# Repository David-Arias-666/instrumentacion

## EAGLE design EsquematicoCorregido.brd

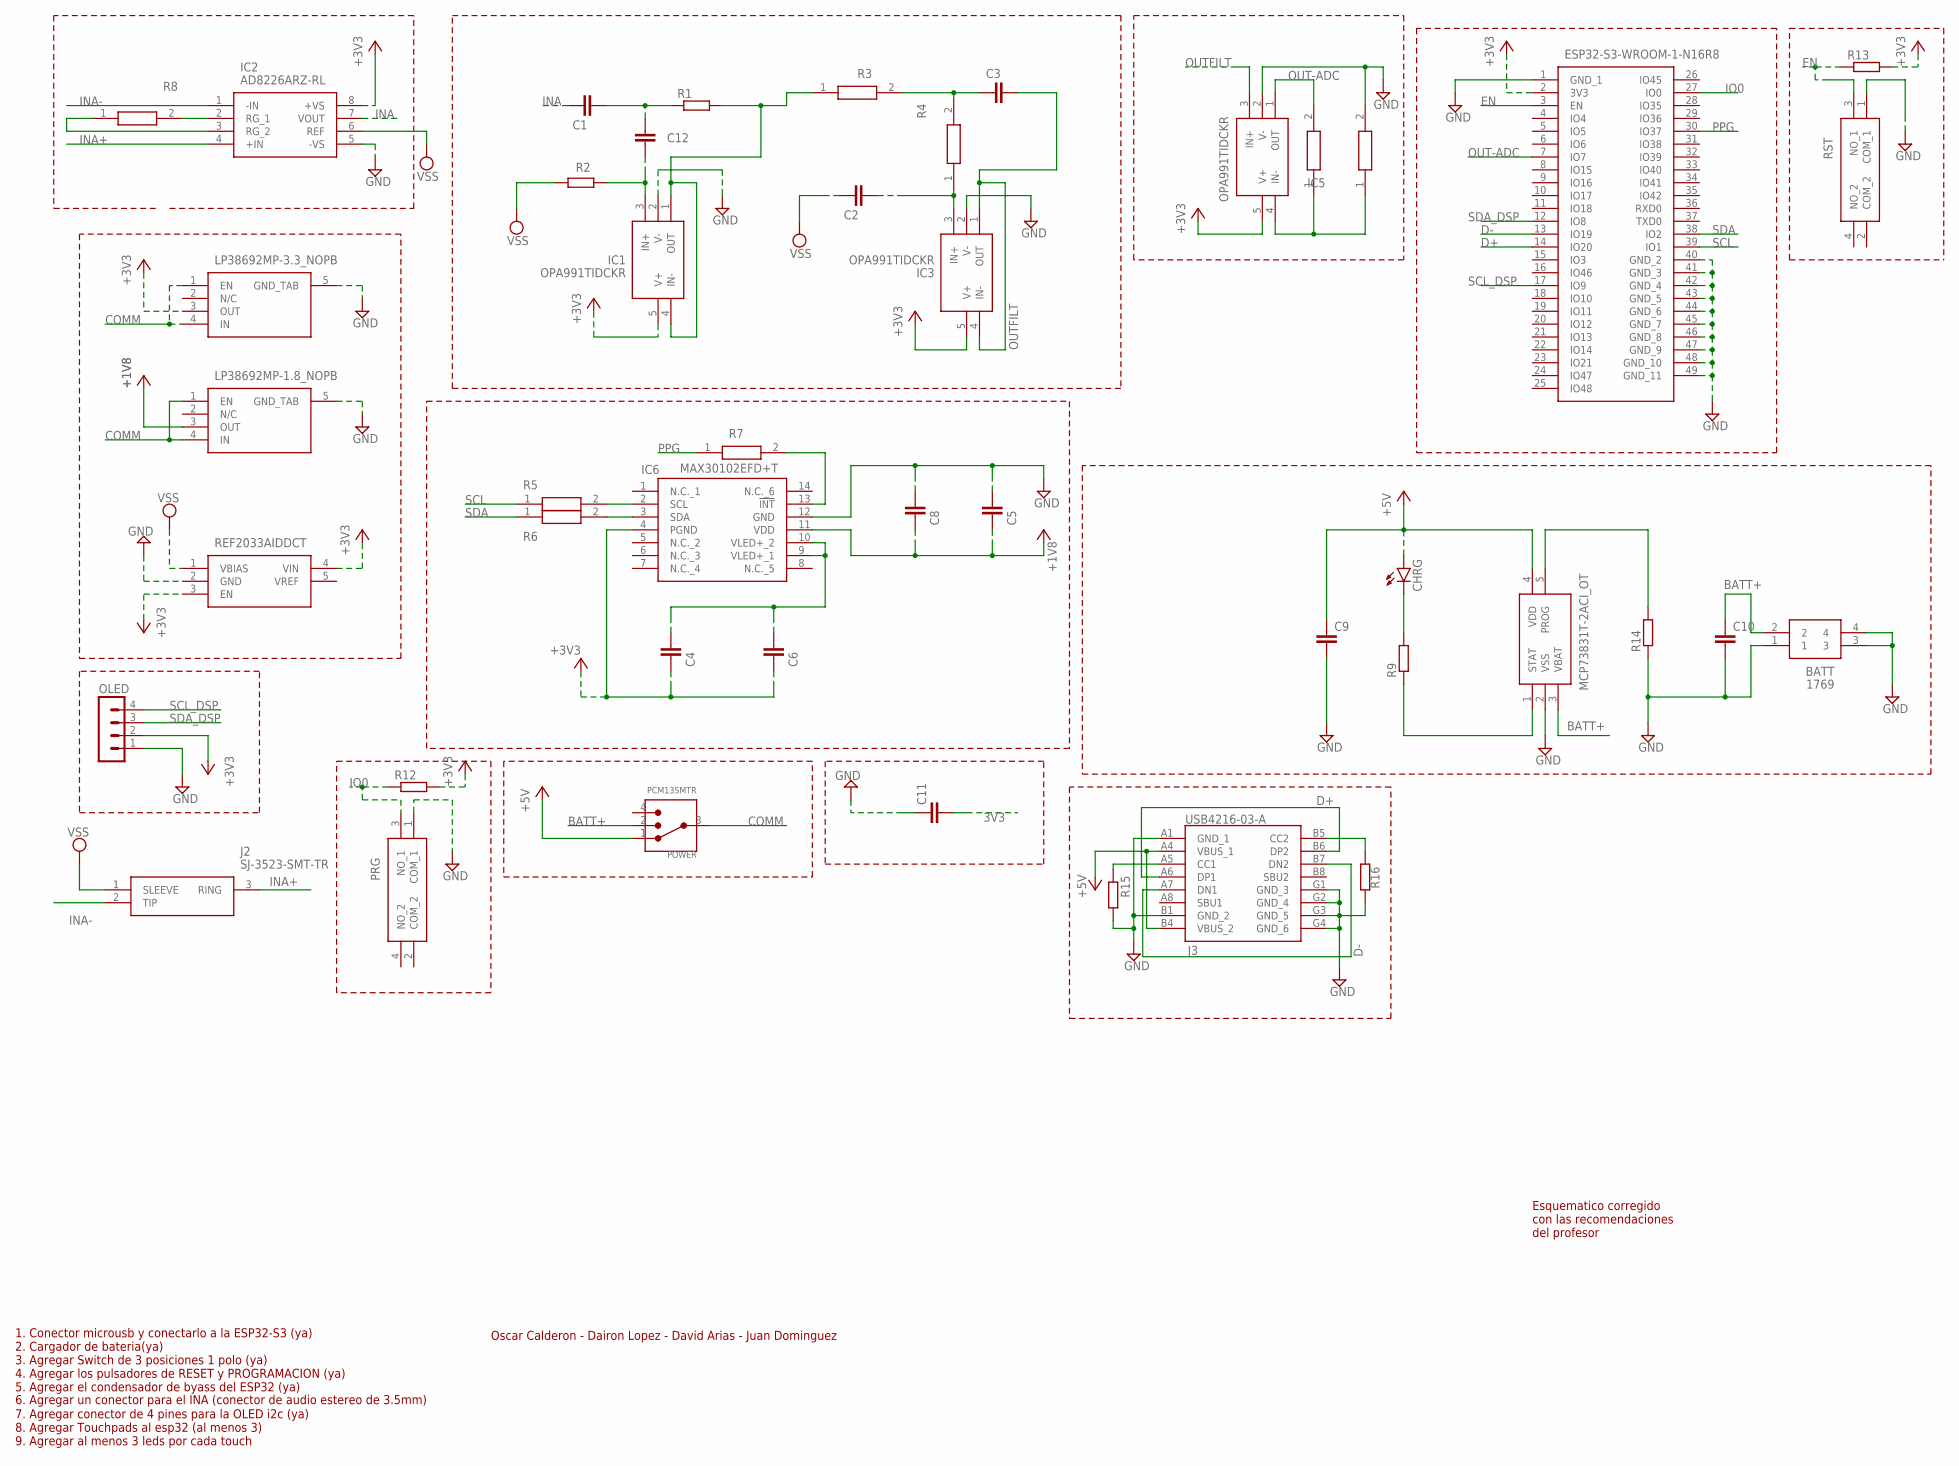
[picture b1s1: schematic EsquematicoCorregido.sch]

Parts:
BATT: 1769
C1, C2, C3, C4, C5, C6, C8, C9, C10, C11, C12: C-EUC0805; C0805
CHRG: LEDCHIP-LED0805; CHIP-LED0805
IC1, IC3, IC5: OPA991TIDCKR; SOT65P210X110-5N
IC2: AD8226ARZ-RL; SOIC127P600X175-8N
IC4: ESP32-S3-WROOM-1-N16R8; ESP32S3WROOM1N16R8
IC6: MAX30102EFD+T; MAX30102EFDT
IC7: LP38692MP-3.3_NOPB; SOT150P700X180-5N
IC8: LP38692MP-1.8_NOPB; SOT150P700X180-5N
IC9: REF2033AIDDCT; SOT95P280X110-5N
IC10: MCP73831T-2ACI_OT; SOT95P270X145-5N
J2: SJ-3523-SMT-TR; SJ3523SMTTR
J3: USB4216-03-A; USB421603A
OLED: MA04-1
POWER: PCM13SMTR; SW_PCM13SMTR
PRG: PTS526SK15SMTR2_LFS; PTS526SK15SMTR2LFS
R1, R2, R9, R12, R13, R14, R15, R16: R-EU_R0805; R0805
R3, R4: ERA-6ARW122V; ERA6AEB101V
R5, R6, R7: CRCW08051K00FKTAHP; RESC2012X60N
R8: RN73H1JTTD1043B50; RESC1608X55N
R10, R11: CRCW0805220RFKTAHP; RESC2012X60N
RST: PTS526SK15SMTR2_LFS; PTS526SK15SMTR2LFS

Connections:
+1V8: C5.1, C8.1, IC6.11 (VDD), IC8.3 (OUT)
+5V: C9.1, CHRG.A, IC10.4 (VDD), J3.A4 (VBUS_1), J3.B4 (VBUS_2), POWER.1
BATT+: BATT.2, C10.1, IC10.3 (VBAT), POWER.2
COMM: IC7.1 (EN), IC7.4 (IN), IC8.1 (EN), IC8.4 (IN), POWER.3
D+: IC4.14 (IO20), J3.A6 (DP1), J3.B6 (DP2)
D-: IC4.13 (IO19), J3.A7 (DN1), J3.B7 (DN2)
EN: IC4.3 (EN), R13.1, RST.3 (NO_1)
GND: BATT.1, BATT.3, BATT.4, C5.2, C8.2, C9.2, C10.2, C11.1, IC1.2 (V-), IC2.5 (-VS), IC3.2 (V-), IC4.1 (GND_1), IC4.40 (GND_2), IC4.41 (GND_3), IC4.42 (GND_4), IC4.43 (GND_5), IC4.44 (GND_6), IC4.45 (GND_7), IC4.46 (GND_8), IC4.47 (GND_9), IC4.48 (GND_10), IC4.49 (GND_11), IC5.2 (V-), IC6.12 (GND), IC7.5 (GND_TAB), IC8.5 (GND_TAB), IC9.2 (GND), IC10.2 (VSS), J3.A1 (GND_1), J3.B1 (GND_2), J3.G1 (GND_3), J3.G2 (GND_4), J3.G3 (GND_5), J3.G4 (GND_6), OLED.1, PRG.1 (COM_1), R11.2, R14.1, R15.2, R16.1, RST.1 (COM_1)
INA: C1.1, IC2.7 (VOUT)
INA+: IC2.4 (+IN), J2.3 (RING)
INA-: IC2.1 (-IN), J2.2 (TIP)
IO0: IC4.27 (IO0), PRG.3 (NO_1), R12.1
unnamed: C3.2, R3.2, R4.2
unnamed: C1.2, C12.2, R1.1
unnamed: C12.1, IC1.3 (IN+), R2.2
unnamed: C2.2, IC3.3 (IN+), R4.1
unnamed: IC5.4 (IN-), R10.1, R11.1
unnamed: IC1.1 (OUT), IC1.4 (IN-), R1.2, R3.1
unnamed: IC2.2 (RG_1), R8.2
unnamed: IC6.13 (!INT), R7.2
unnamed: C4.2, C6.2, IC6.9 (VLED+_1), IC6.10 (VLED+_2)
unnamed: IC2.3 (RG_2), R8.1
unnamed: IC6.3 (SDA), R6.2
unnamed: IC6.2 (SCL), R5.2
unnamed: CHRG.C, R9.2
unnamed: J3.A5 (CC1), R15.1
unnamed: IC10.5 (PROG), R14.2
unnamed: IC10.1 (STAT), R9.1
unnamed: J3.B5 (CC2), R16.2
OUT-ADC: IC4.7 (IO7), IC5.1 (OUT), R10.2
OUTFILT: C3.1, IC3.1 (OUT), IC3.4 (IN-), IC5.3 (IN+)
PPG: IC4.30 (IO37), R7.1
SCL: IC4.39 (IO1), R5.1
SCL_DSP: IC4.17 (IO9), OLED.4
SDA: IC4.38 (IO2), R6.1
SDA_DSP: IC4.12 (IO8), OLED.3
VSS: C2.1, IC2.6 (REF), IC9.1 (VBIAS), J2.1 (SLEEVE), R2.1

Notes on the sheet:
Esquematico corregido con las recomendaciones del profesor
Oscar Calderon - Dairon Lopez - David Arias - Juan Dominguez
1. Conector microusb y conectarlo a la ESP32-S3 (ya) 2. Cargador de bateria(ya) 3. Agregar Switch de 3 posiciones 1 polo (ya) 4. Agregar los pulsadores de RESET y PROGRAMACION (ya) 5. Agregar el condensador de byass del ESP32 (ya)
6. Agregar un conector para el INA (conector de audio estereo de 3.5mm)
7. Agregar conector de 4 pines para la OLED i2c (ya) 8. Agregar Touchpads al esp32 (al menos 3) 9. Agregar al menos 3 leds por cada touch

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
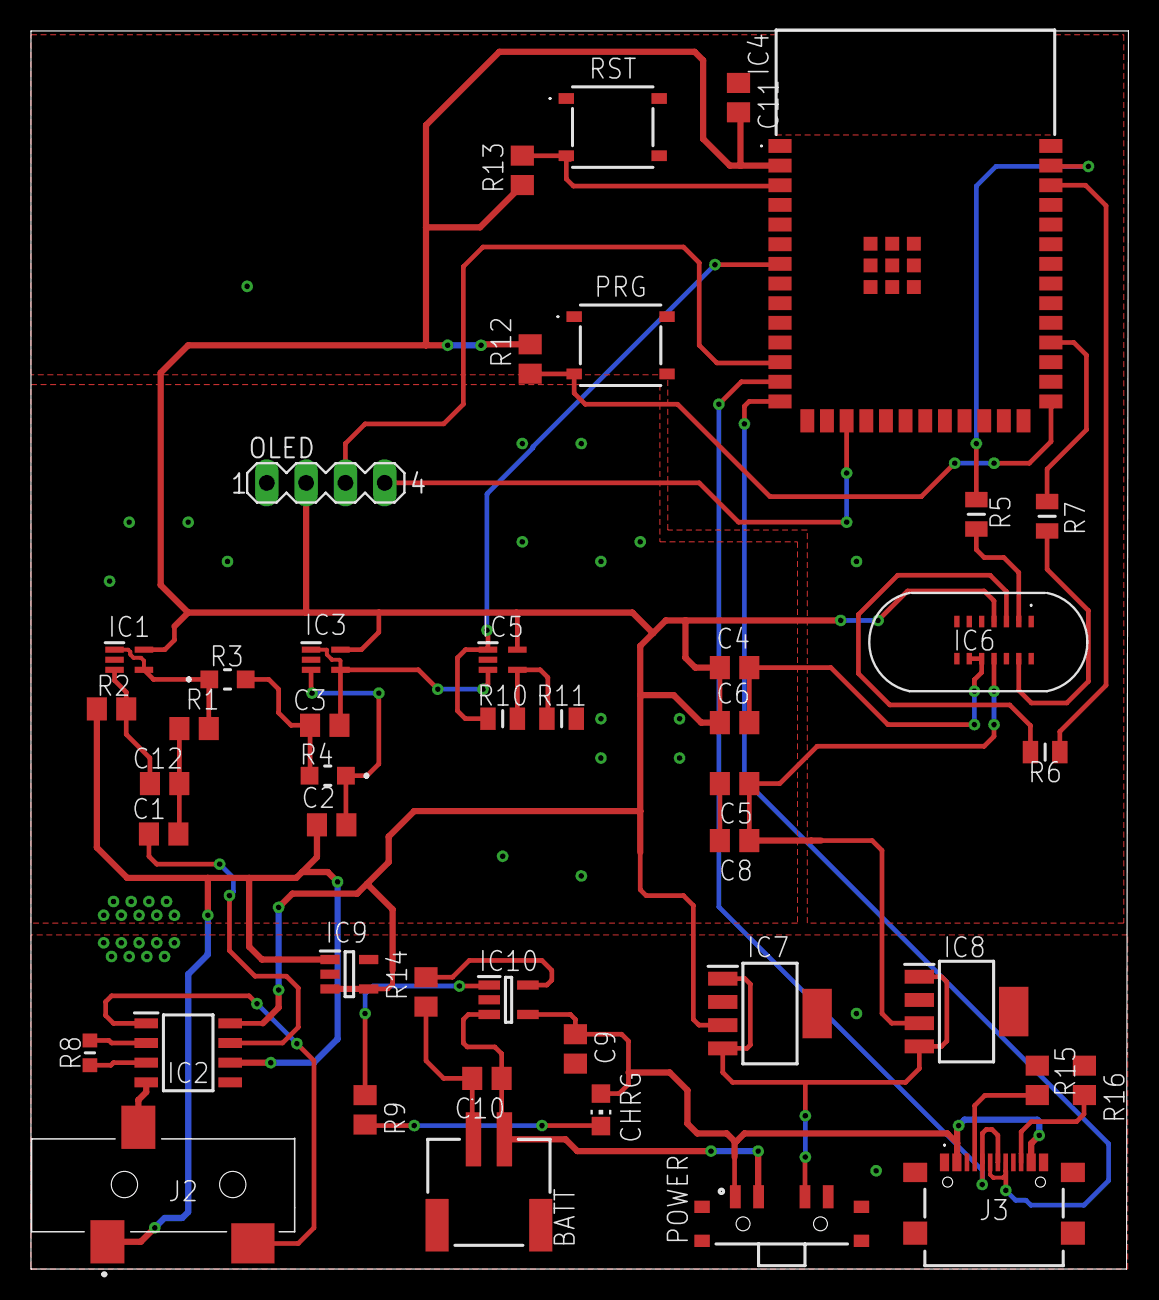
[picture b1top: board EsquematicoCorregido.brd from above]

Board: 2 copper layers, 70.9 x 80.0 mm, 45 parts (0 on the bottom side), 38 nets.

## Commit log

2025-10-03 Create max301002
2025-10-03 Se corrigieron algunas cosas en el esquematico
2025-10-06 Esquematico corregido con las recomendaciones del profesor
2025-10-10 Componentes.md
2025-10-10 Hojas de datos
2025-10-10 correciones
2025-10-10 Se corrigieron algunos bloques y se anoto lo faltante
2025-10-13 Informe proyecto integrador Segundo corte
2025-10-31 ultima actualización, correcion de los puntos
2025-10-31 Se corrigio el esquematico y packages
2025-11-05 ultimas actualizaciones
2025-11-05 fix: PCB and schematic errors fixed
2025-11-06 Avance PCB
2025-11-06 modificaciones PCB
2025-11-07 Mas pistas a la PCB
2025-11-07 Pistas del conector micro usb-c
2025-11-07 pines de tierra GND
2025-11-07 tierras de la PCB
2025-11-07 actualizaciones de la PCB
2025-11-07 corrección de pistas
2025-11-07 ultimo avance
2025-11-21 avances
2025-11-21 aporte PCB
2025-11-21 correcciones en esquematico
2025-11-21 Ultimos detalles
